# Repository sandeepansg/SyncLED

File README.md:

<h1 align="center"> SyncLED </h1> <br>

## Table of Contents

- [Introduction](#introduction)
- [Features](#features)
- [Feedback](#feedback)
- [Contributors](#contributors)
- [License](#license)
- [Acknowledgments](#acknowledgments)

## Introduction

SyncLED is a implementation of a basic secure communication framework to bridge between a host software and a slave LED controller. The host software grabs the bus reported temperature data using [Open Hardware Monitor Library](https://github.com/SandeepanSengupta/SyncLED/blob/master/Sources/Application/Bridge/New/OpenHardwareMonitorLib.dll) and sends it over the usb to the salve embedded led controller using the self-tailored secure communication format.
<p align="center">
  
</p>

<p align="center">
  Screenshot of host software.
</p>

## Features
- Real-time temperature monitoring of CPU and GPU
- Temperature dependent LED control
- Independent Host software

## Social
Connect us here:
<br><br>
 <br>
 
<p> 
or <a href ="https://github.com/TamojitSaha/LTC2633/issues/new/">file an issue</a>. Feature requests are always welcome.</p>

## License
Contents of this repository are realeased under [CC-BY-NC-SA 4.0](./LICENSE.md) <br>

## Acknowledgments

Thanks to [Google](https://www.google.com) and various developers for supporting us with a tons of developments... :wink:

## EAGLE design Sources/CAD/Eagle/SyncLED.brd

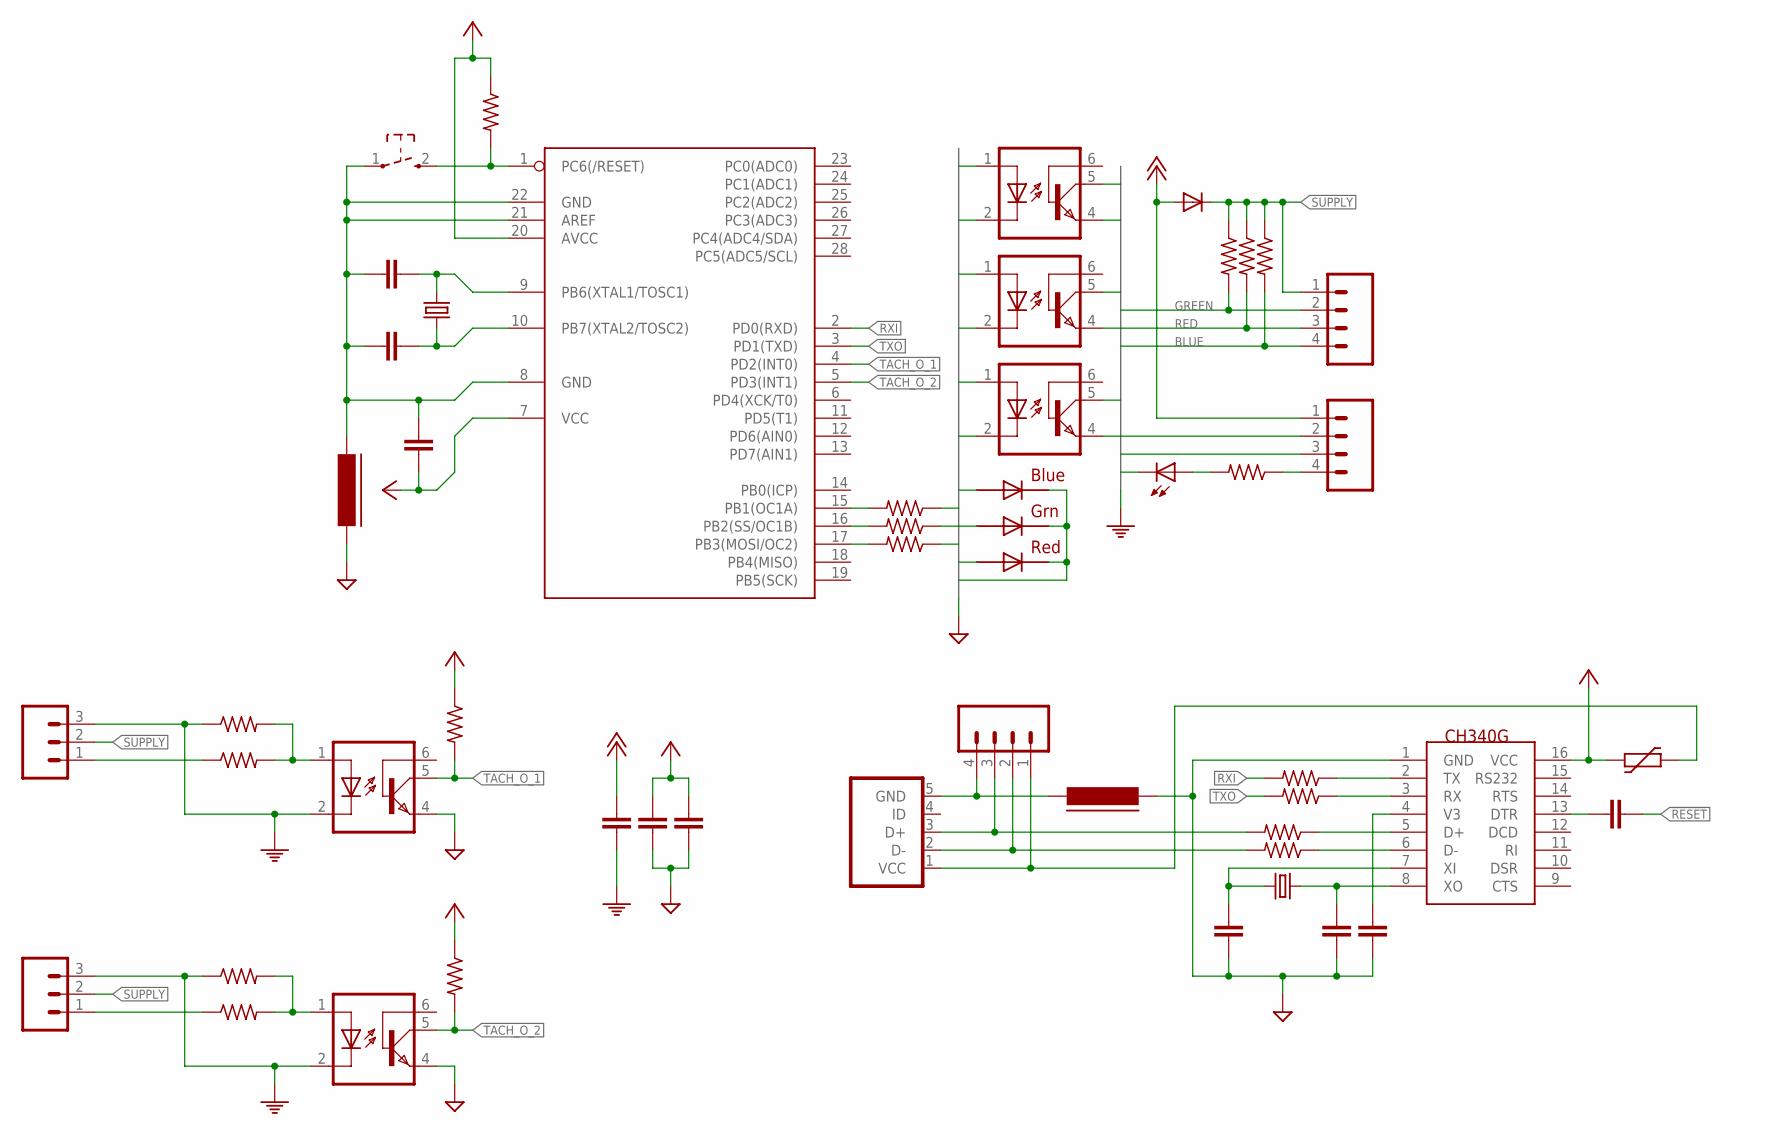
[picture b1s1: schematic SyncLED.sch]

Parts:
!RES: SMD; SW_TACT_3X6
C1, C2, C3, C4: 22pF; C0805K
CAP_!DTR: 100nF; C1206K
CAP_BYPASS: 22pF; C0805K
CAP_DIGITAL_1, CAP_DIGITAL_2: 1uF; C1210K
CAP_LED: 1uF; C1206K
CAP_MCU: 10uF; C1206K
DIODE_LED: 1N4004; DO41-10
FAN_HEADER_1, FAN_HEADER_2: M03PTH; 1X03
FERRITE_MCU: UGND; FB805
FERRITE_USB: UGND; FB805
INDICATOR: RGBLED5050
LED_OUTPUT: M04PTH; 1X04
MCU: MEGA8-P; DIL28-3
OPTO_BLUE: 4N35; DIL06
OPTO_GREEN: 4N35; DIL06
OPTO_RED: 4N35; DIL06
OPTO_TACH_1, OPTO_TACH_2: 4N35; DIL06
POWER_INDICATOR: LEDCHIPLED_1206; CHIPLED_1206
PPTC: 500mA; PTC0805
RES_BLUE: 10K; 0207/10
RES_B_IN: 100E; 0207/12
RES_D+: 100E; M0805
RES_D-: 100E; M0805
RES_GREEN: 10K; 0207/10
RES_G_IN: 100E; 0207/12
RES_LED: 10K; M1206
RES_PULLUP: 10K; 0207/12
RES_RED: 10K; 0207/10
RES_RX: 100E; 0207/10
RES_R_IN: 100E; 0207/12
RES_TACH_1, RES_TACH_2: 100E; 0207/10
RES_TACH_PULLDOWN_1, RES_TACH_PULLDOWN_2: 1K; 0207/10
RES_TACH_PULLUP_1, RES_TACH_PULLUP_2: 10K; 0207/10
RES_TX: 100E; 0207/10
SMPS_SUPPLY: M04PTH; 1X04
USB2UART: CH340G; SOIC16
USB-RECEPTABLE: USB-Micro; FCI-10103594-0001LF
USB_PORT: M04PTH; 1X04
XTAL_MCU: CRYSTALHC49S; HC49/S
XTAL_USB: CRYSTALHC49S; HC49/S

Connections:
3V: CAP_BYPASS.1, USB2UART.4 (V3)
!DTR: CAP_!DTR.1, USB2UART.13 (DTR)
!RESET: !RES.2 (3), CAP_!DTR.2, MCU.1 (PC6(/RESET)), RES_PULLUP.2
+5V: CAP_DIGITAL_1.1, CAP_DIGITAL_2.1, CAP_MCU.1, MCU.7 (VCC), MCU.20 (AVCC), PPTC.1, RES_PULLUP.1, RES_TACH_PULLUP_1.1, RES_TACH_PULLUP_2.1, USB2UART.16 (VCC)
+12V: CAP_LED.1, DIODE_LED.A, SMPS_SUPPLY.1
BLUE: LED_OUTPUT.4, OPTO_BLUE.5 (COL), RES_BLUE.2
B_IN: MCU.17 (PB3(MOSI/OC2)), RES_B_IN.2
B_OUT: INDICATOR.3 (BLUE_A), OPTO_BLUE.1 (A), RES_B_IN.1
DGND: C1.2, C2.2, CAP_BYPASS.2, CAP_DIGITAL_1.2, CAP_DIGITAL_2.2, FERRITE_MCU.1, FERRITE_USB.2, INDICATOR.4 (BLUE_C), INDICATOR.5 (RED_C), INDICATOR.6 (GREEN_C), OPTO_BLUE.2 (C), OPTO_GREEN.2 (C), OPTO_RED.2 (C), OPTO_TACH_1.4 (EMI), OPTO_TACH_2.4 (EMI), USB2UART.1 (GND)
DI_I: RES_D+.2, USB-RECEPTABLE.3 (D+), USB_PORT.3
DI_O: RES_D-.2, USB-RECEPTABLE.2 (D-), USB_PORT.2
DO_N: RES_D-.1, USB2UART.6 (D-)
DO_P: RES_D+.1, USB2UART.5 (D+)
GREEN: LED_OUTPUT.2, OPTO_GREEN.5 (COL), RES_RED.2
GROUND: CAP_LED.2, FAN_HEADER_1.3, FAN_HEADER_2.3, OPTO_BLUE.4 (EMI), OPTO_GREEN.4 (EMI), OPTO_RED.4 (EMI), OPTO_TACH_1.2 (C), OPTO_TACH_2.2 (C), POWER_INDICATOR.C, RES_TACH_PULLDOWN_1.1, RES_TACH_PULLDOWN_2.1, SMPS_SUPPLY.2, SMPS_SUPPLY.3
G_IN: MCU.16 (PB2(SS/OC1B)), RES_G_IN.2
G_OUT: INDICATOR.1 (GREEN_A), OPTO_GREEN.1 (A), RES_G_IN.1
LED_SUPPLY: POWER_INDICATOR.A, RES_LED.2
MCU_GND: !RES.1, C3.1, C4.1, CAP_MCU.2, FERRITE_MCU.2, MCU.8 (GND), MCU.21 (AREF), MCU.22 (GND)
MCU_XI: C3.2, MCU.9 (PB6(XTAL1/TOSC1)), XTAL_MCU.2
MCU_XO: C4.2, MCU.10 (PB7(XTAL2/TOSC2)), XTAL_MCU.1
RED: LED_OUTPUT.3, OPTO_RED.5 (COL), RES_GREEN.2
RXI: MCU.2 (PD0(RXD)), RES_TX.2
RXO: RES_RX.1, USB2UART.3 (RX)
R_IN: MCU.15 (PB1(OC1A)), RES_R_IN.2
R_OUT: INDICATOR.2 (RED_A), OPTO_RED.1 (A), RES_R_IN.1
SUPPLY: DIODE_LED.C, FAN_HEADER_1.2, FAN_HEADER_2.2, LED_OUTPUT.1, RES_BLUE.1, RES_GREEN.1, RES_RED.1
SUPPLY_5V: RES_LED.1, SMPS_SUPPLY.4
TACH_IN_1: FAN_HEADER_1.1, RES_TACH_1.1
TACH_IN_2: FAN_HEADER_2.1, RES_TACH_2.1
TACH_OPTO_1: OPTO_TACH_1.1 (A), RES_TACH_1.2, RES_TACH_PULLDOWN_1.2
TACH_OPTO_2: OPTO_TACH_2.1 (A), RES_TACH_2.2, RES_TACH_PULLDOWN_2.2
TACH_O_1: MCU.4 (PD2(INT0)), OPTO_TACH_1.5 (COL), RES_TACH_PULLUP_1.2
TACH_O_2: MCU.5 (PD3(INT1)), OPTO_TACH_2.5 (COL), RES_TACH_PULLUP_2.2
TXI: RES_TX.1, USB2UART.2 (TX)
TXO: MCU.3 (PD1(TXD)), RES_RX.2
USB_GND: FERRITE_USB.1, USB-RECEPTABLE.5 (GND), USB_PORT.4
USB_XI: C2.1, USB2UART.7 (XI), XTAL_USB.1
USB_XO: C1.1, USB2UART.8 (XO), XTAL_USB.2
VUSB: PPTC.2, USB-RECEPTABLE.1 (VCC), USB_PORT.1

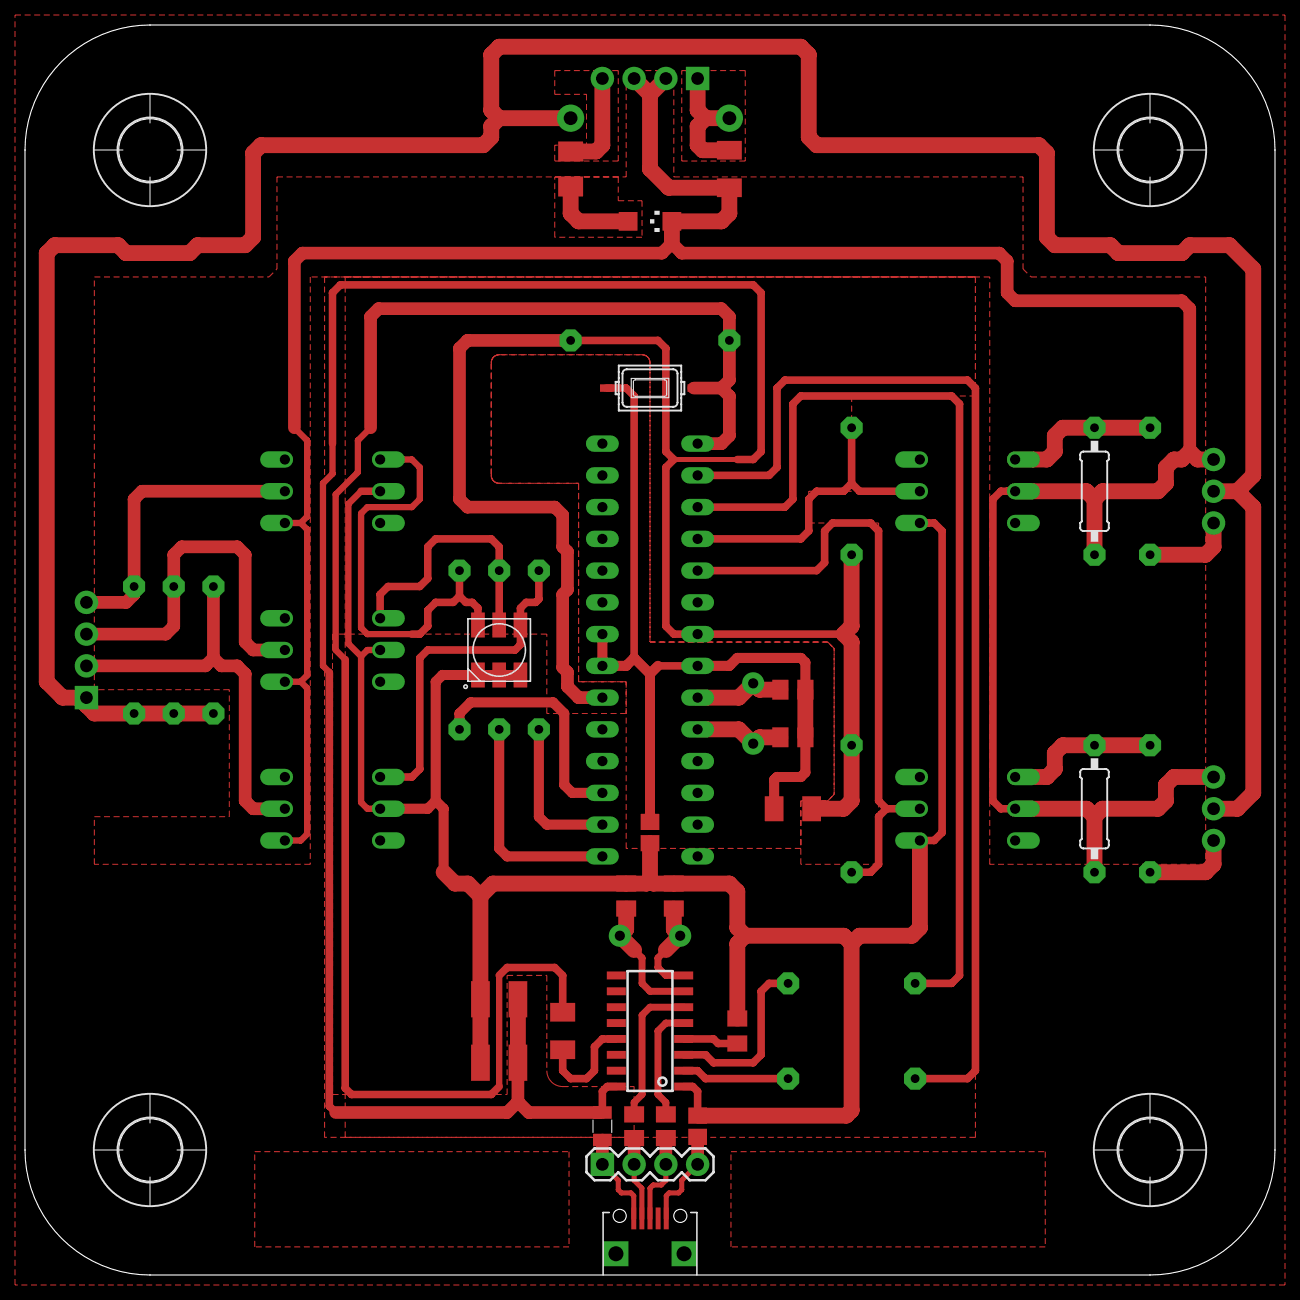
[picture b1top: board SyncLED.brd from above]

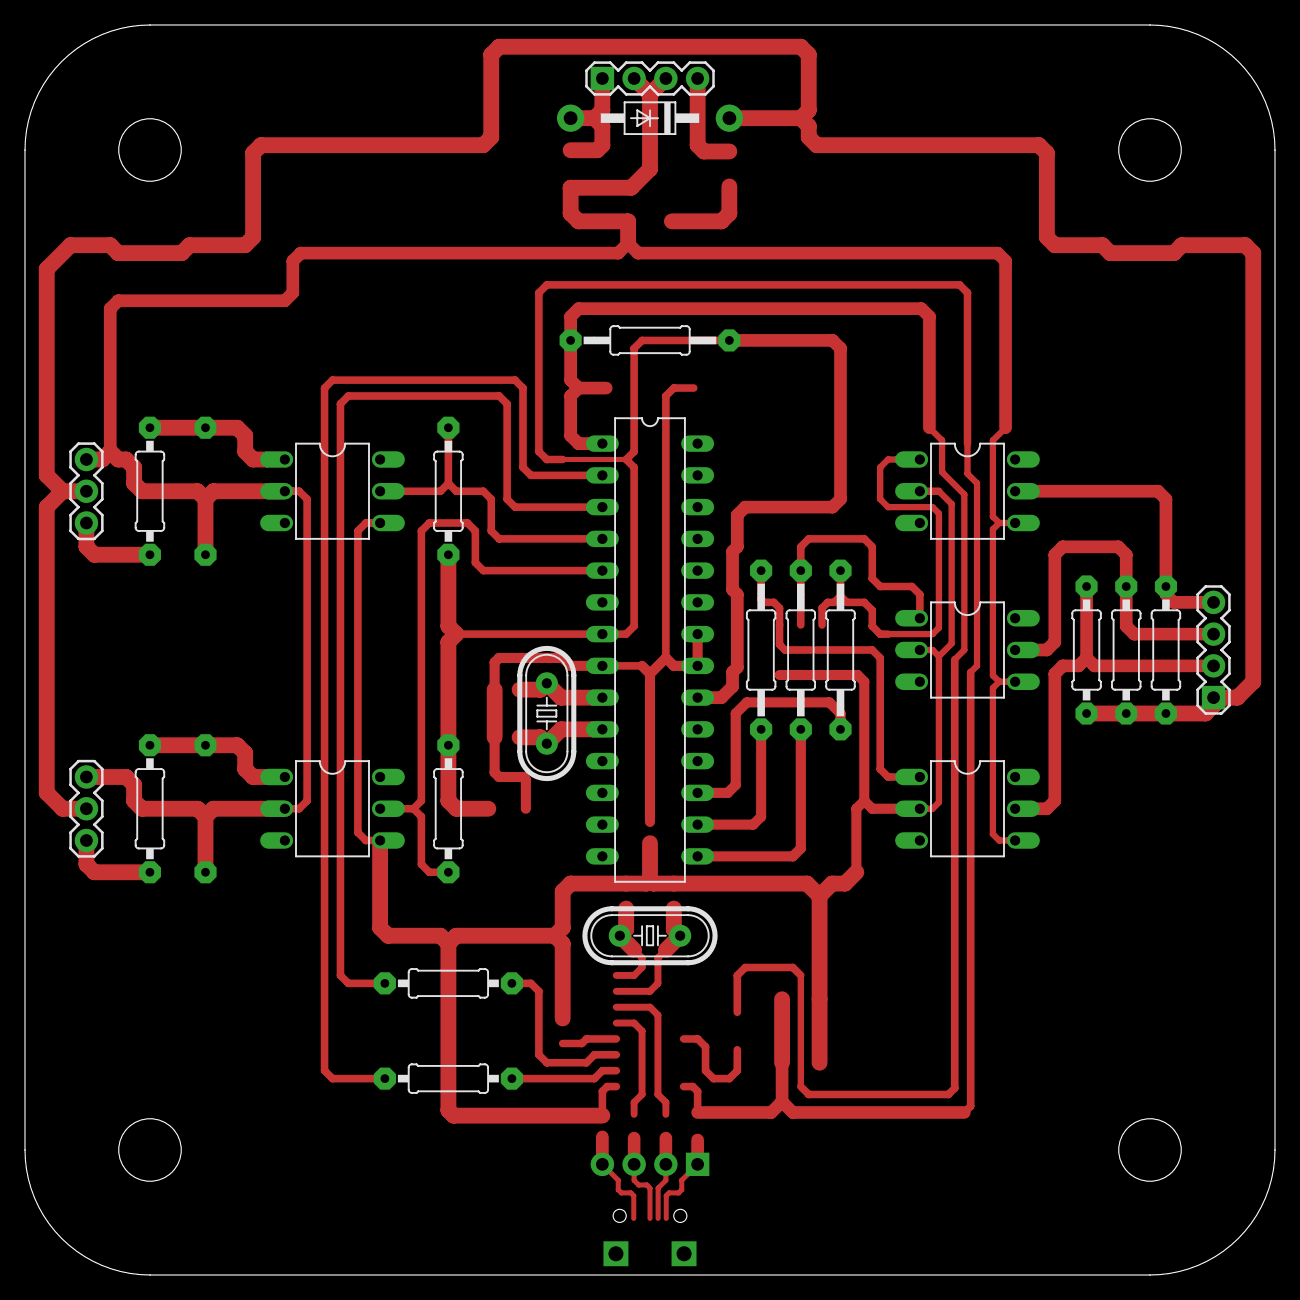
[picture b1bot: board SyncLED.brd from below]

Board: 2 copper layers, 100.0 x 100.0 mm, 54 parts (26 on the bottom side), 40 nets.

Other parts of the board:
U$1, U$2, U$3, U$5: 5,0

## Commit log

2018-02-10 Added new images
    Device and application image added

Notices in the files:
Sources/CAD/Eagle/SyncLED.brd:
CopyRight (C) 2016
parts and their libraries:
SparkFun-Connectors: Licensing: Creative Commons ShareAlike 4.0 International - https://creativecommons.org/licenses/by-sa/4.0
